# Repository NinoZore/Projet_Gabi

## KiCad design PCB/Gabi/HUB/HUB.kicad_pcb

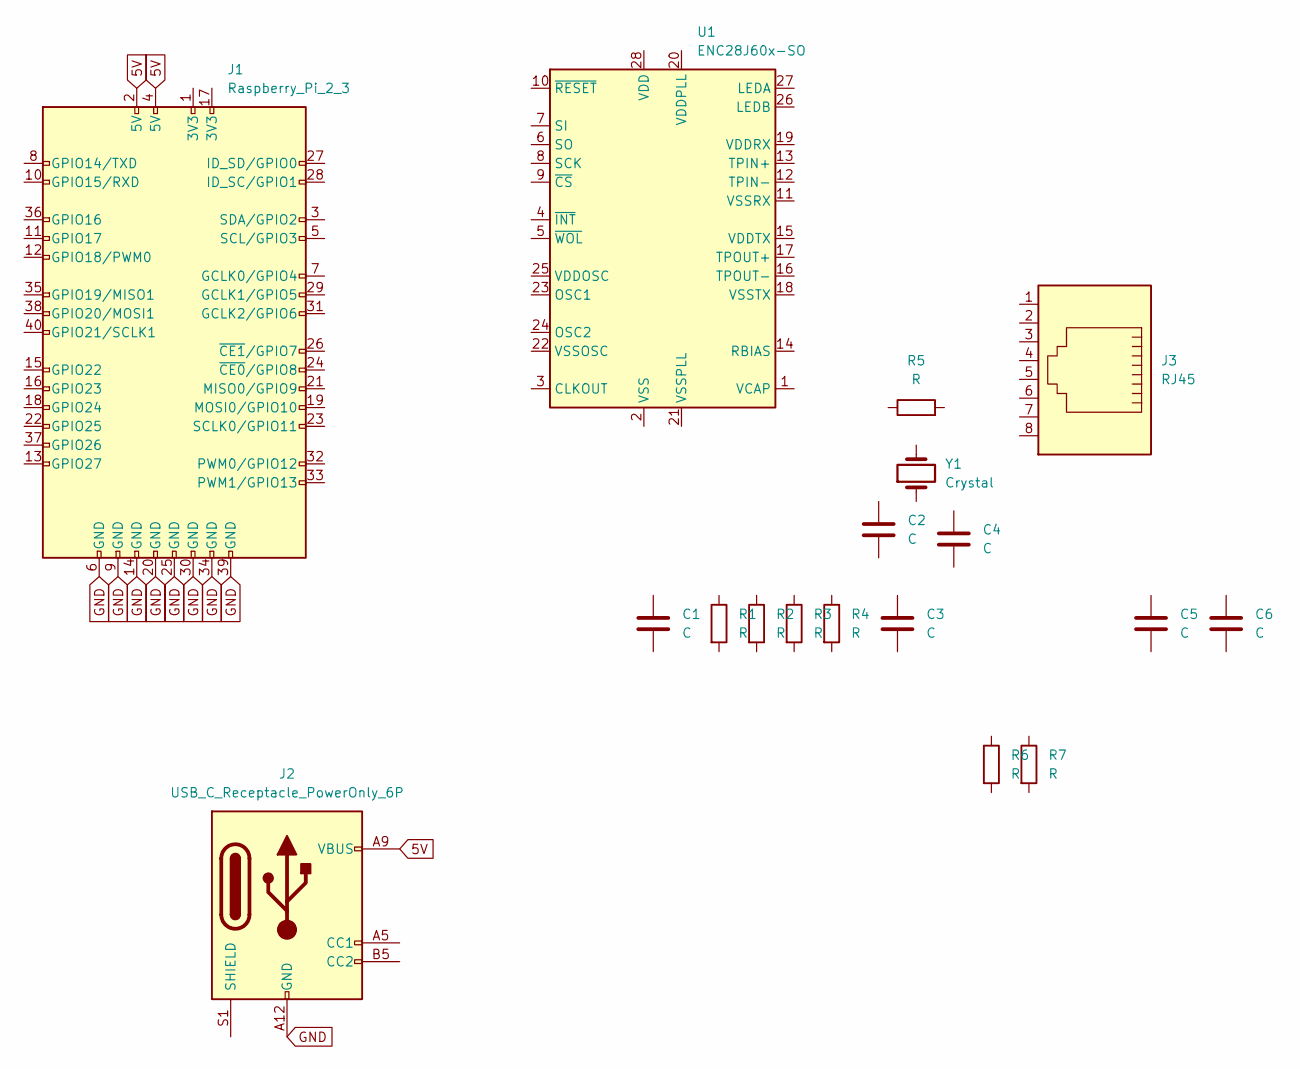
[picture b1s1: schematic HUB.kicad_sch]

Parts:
C1, C2, C4, C5, C6: C; C_0201_0603Metric
C3: C
J1: Raspberry_Pi_2_3
J2: USB_C_Receptacle_PowerOnly_6P; USB_C_Plug_Molex_105444
J3: RJ45
R1, R2, R3, R5, R6, R7: R; R_0201_0603Metric
R4: R
U1: ENC28J60x-SO; SOIC-28W_7.5x17.9mm_P1.27mm
Y1: Crystal

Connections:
5V: J1.2 (5V), J1.4 (5V), J2.A9 (VBUS), J2.B9 (VBUS)
GND: J1.6 (GND), J1.9 (GND), J1.14 (GND), J1.20 (GND), J1.25 (GND), J1.30 (GND), J1.34 (GND), J1.39 (GND), J2.A12 (GND), J2.B12 (GND)

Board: 2 copper layers, 18 parts (0 on the bottom side), 2 nets, no tracks yet.

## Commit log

2023-01-06 First commit ajout des bases
2023-01-06 Commit des doc des Programs et update main
2023-01-06 ajout 3d model d'example
2023-01-06 schéma drawio
2023-01-07 avance pcb
2023-01-08 update PCB
2023-01-08 commit update pcb
2023-01-10 PCB UPDATE
